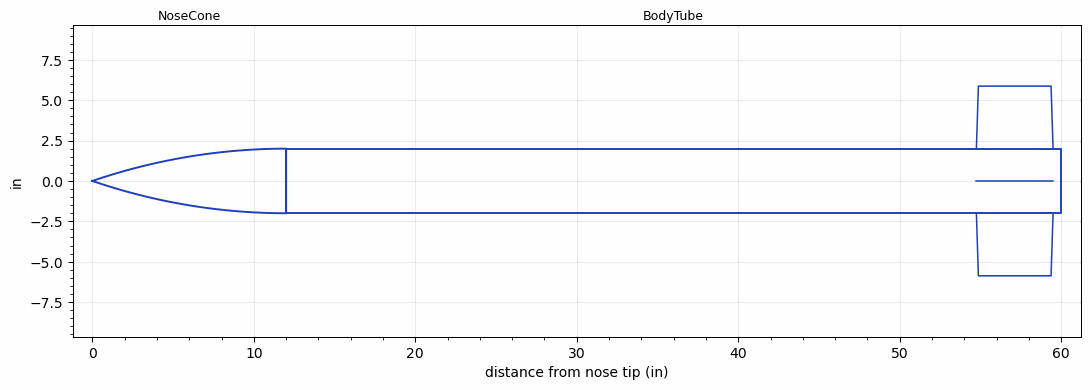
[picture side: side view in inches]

<RASAeroDocument>
 <FileVersion>2</FileVersion>
 <RocketDesign>
  <NoseCone>
   <Length>12</Length>
   <Diameter>4</Diameter>
   <Shape>Tangent Ogive</Shape>
   <Location>0</Location>
  </NoseCone>
  <BodyTube>
   <Length>48</Length>
   <Diameter>4</Diameter>
   <Location>12</Location>
   <Fin>
    <Count>4</Count>
    <Chord>4.75</Chord>
    <Span>3.875</Span>
    <SweepDistance>0.125</SweepDistance>
    <TipChord>4.5</TipChord>
    <Thickness>0.125</Thickness>
    <Location>5.25</Location>
    <AirfoilSection>Square</AirfoilSection>
   </Fin>
  </BodyTube>
  <Surface>Smooth (Zero Roughness)</Surface>
  <ModifiedBarrowman>False</ModifiedBarrowman>
  <Turbulence>True</Turbulence>
  <UseBooster1>False</UseBooster1>
  <UseBooster2>False</UseBooster2>
  <Comments>Final independent static CP evaluation, four-fin-near-rectangular</Comments>
 </RocketDesign>
 <LaunchSite>
  <Altitude>0</Altitude>
  <Pressure>29.9214</Pressure>
  <RodAngle>0</RodAngle>
  <RodLength>6.5617</RodLength>
  <Temperature>59</Temperature>
  <WindSpeed>0</WindSpeed>
 </LaunchSite>
 <Recovery>
  <Altitude1>0</Altitude1>
  <Altitude2>0</Altitude2>
  <DeviceType1>None</DeviceType1>
  <DeviceType2>None</DeviceType2>
  <Event1>False</Event1>
  <Event2>False</Event2>
  <Size1>0</Size1>
  <Size2>0</Size2>
  <EventType1>None</EventType1>
  <EventType2>None</EventType2>
  <CD1>0</CD1>
  <CD2>0</CD2>
 </Recovery>
</RASAeroDocument>
